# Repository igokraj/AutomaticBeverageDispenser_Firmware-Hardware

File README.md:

# Automatic Beverage Dispenser

A complete hardware and software solution for an automated beverage dispensing system. The project features a custom 2-layer printed circuit board (PCB) and firmware written in C for the STM32G0 microcontroller. The system accurately dispenses liquids by measuring the flow rate via a dedicated sensor and controlling a 12V fluid pump.

## Features
* **Adjustable Volume Control:** Users can set the desired liquid volume between 50 ml and 300 ml (in 50 ml increments) using the "Up" and "Down" tactile switches.
* **Precise Dispensing:** Utilizes an external flow sensor with interrupt-driven pulse counting to accurately measure the dispensed volume based on a configurable K-factor.
* **Automated Pump Control:** The MCU controls a 12V DC fluid pump via an onboard N-channel MOSFET (AO3400), automatically shutting it off once the target volume is reached.
* **Emergency Stop:** The pouring process can be manually halted at any time by pressing the "Start/Stop" button.
* **Expansion Ready:** Exposed I2C headers allow for future integration of external modules, such as an OLED display.

## Hardware Specifications
* **Microcontroller:** STM32G030F6P6 (ARM Cortex-M0+)
* **Power Supply:** 12V DC input (barrel jack), regulated to 3.3V for logic via an AMS1117 LDO.
* **Actuator Driver:** AO3400 MOSFET with flyback diode protection for the 12V pump.
* **Inputs:** 3x Tactile switches (hardware debounced/filtered), 1x Flow sensor signal input.
* **Interfaces:** SWD programming header, I2C expansion header.

## Software
The firmware is developed using STM32 HAL. It implements a simple state machine (`IDLE` and `POURING`) to manage user inputs and the dispensing process. Button inputs are software-debounced, and the flow sensor is handled via external interrupts (EXTI) to ensure no pulses are missed during the pump operation.

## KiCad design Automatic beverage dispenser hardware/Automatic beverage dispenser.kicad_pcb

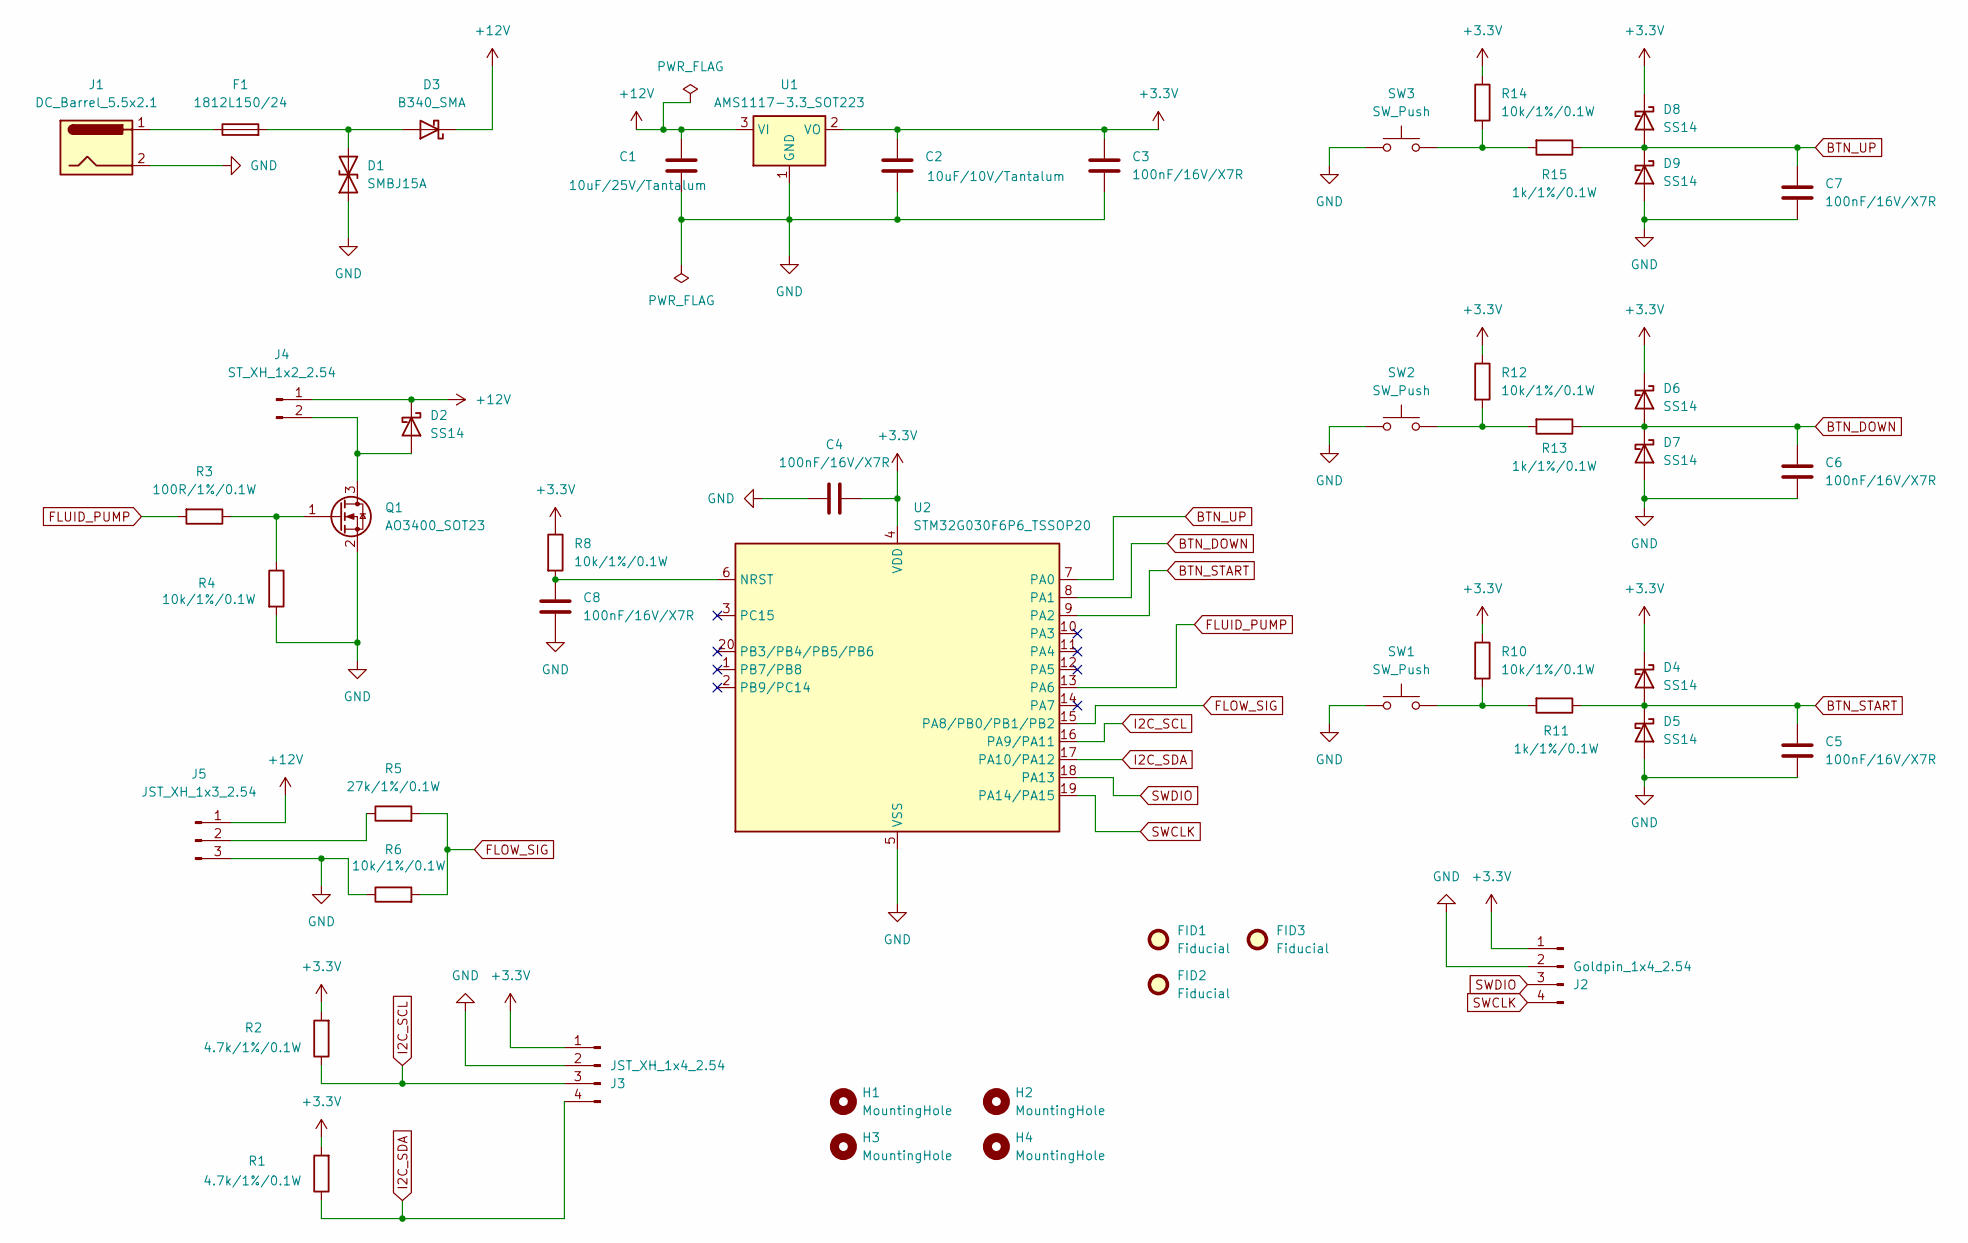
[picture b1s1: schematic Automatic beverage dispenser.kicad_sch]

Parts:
C1: 10uF/25V/Tantalum; CP_EIA-3216-18_Kemet-A; LCSC Part # C13585
C2: 10uF/10V/Tantalum; CP_EIA-3216-18_Kemet-A; LCSC Part # C7177
C3, C4, C5, C6, C7, C8: 100nF/16V/X7R; C_0805_2012Metric; LCSC Part # C49678
D1: SMBJ15A; D_SMB; LCSC Part # C10210
D2, D4, D5, D6, D7, D8, D9: SS14; D_SMA; LCSC Part # C2168
D3: B340_SMA; D_SMA; LCSC Part # C64982
F1: 1812L150/24; Fuse_1812_4532Metric; LCSC Part # C9308
FID1, FID2, FID3: Fiducial; Fiducial_1mm_Mask2mm
H1, H2, H3, H4: MountingHole; MountingHole_2.2mm_M2
J1: DC_Barrel_5.5x2.1; BarrelJack_Horizontal
J2: Goldpin_1x4_2.54; PinHeader_1x04_P2.54mm_Vertical
J3: JST_XH_1x4_2.54; JST_XH_B4B-XH-A_1x04_P2.50mm_Vertical
J4: ST_XH_1x2_2.54; JST_XH_B2B-XH-A_1x02_P2.50mm_Vertical
J5: JST_XH_1x3_2.54; JST_XH_B3B-XH-A_1x03_P2.50mm_Vertical
Q1: AO3400_SOT23; SOT-23; LCSC Part # C20917
R1, R2: 4.7k/1%/0.1W; R_0805_2012Metric; LCSC Part # C17673
R3: 100R/1%/0.1W; R_0805_2012Metric; LCSC Part # C17408
R4, R6, R8, R10, R12, R14: 10k/1%/0.1W; R_0805_2012Metric; LCSC Part # C17414
R5: 27k/1%/0.1W; R_0805_2012Metric; LCSC Part # C2904543
R11, R13, R15: 1k/1%/0.1W; R_0805_2012Metric; LCSC Part # C17513
SW1, SW2, SW3: SW_Push; SW_PUSH_6mm_H5mm
U1: AMS1117-3.3_SOT223; SOT-223-3_TabPin2; LCSC Part # C6186
U2: STM32G030F6P6_TSSOP20; TSSOP-20_4.4x6.5mm_P0.65mm; LCSC Part # C529330

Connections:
+3.3V: C2.1, C3.1, C4.2, D4.1 (K), D6.1 (K), D8.1 (K), J2.1, J3.1, R1.2, R2.2, R8.1, R10.1, R12.1, R14.1, U1.2 (VO), U2.4 (VDD)
+12V: C1.1, D2.1 (K), D3.1 (K), J4.1, J5.1, U1.3 (VI)
BTN_DOWN: C6.2, D6.2 (A), D7.1 (K), R13.1, U2.8 (PA1)
BTN_START: C5.2, D4.2 (A), D5.1 (K), R11.1, U2.9 (PA2)
BTN_UP: C7.2, D8.2 (A), D9.1 (K), R15.1, U2.7 (PA0)
FLOW_SIG: R5.2, R6.2, U2.15 (PA8/PB0/PB1/PB2)
FLUID_PUMP: R3.2, U2.13 (PA6)
GND: C1.2, C2.2, C3.2, C4.1, C5.1, C6.1, C7.1, C8.1, D1.1 (A1), D5.2 (A), D7.2 (A), D9.2 (A), J1.2, J2.2, J3.2, J5.3, Q1.2 (S), R4.2, R6.1, SW1.1, SW2.1, SW3.1, U1.1 (GND), U2.5 (VSS)
I2C_SCL: J3.3, R2.1, U2.16 (PA9/PA11)
I2C_SDA: J3.4, R1.1, U2.17 (PA10/PA12)
unnamed: D1.2 (A2), D3.2 (A), F1.2
unnamed: D2.2 (A), J4.2, Q1.3 (D)
unnamed: F1.1, J1.1
unnamed: J5.2, R5.1
unnamed: Q1.1 (G), R3.1, R4.1
unnamed: R10.2, R11.2, SW1.2
unnamed: R12.2, R13.2, SW2.2
unnamed: R14.2, R15.2, SW3.2
unnamed: C8.2, R8.2, U2.6 (NRST)
SWCLK: J2.4, U2.19 (PA14/PA15)
SWDIO: J2.3, U2.18 (PA13)

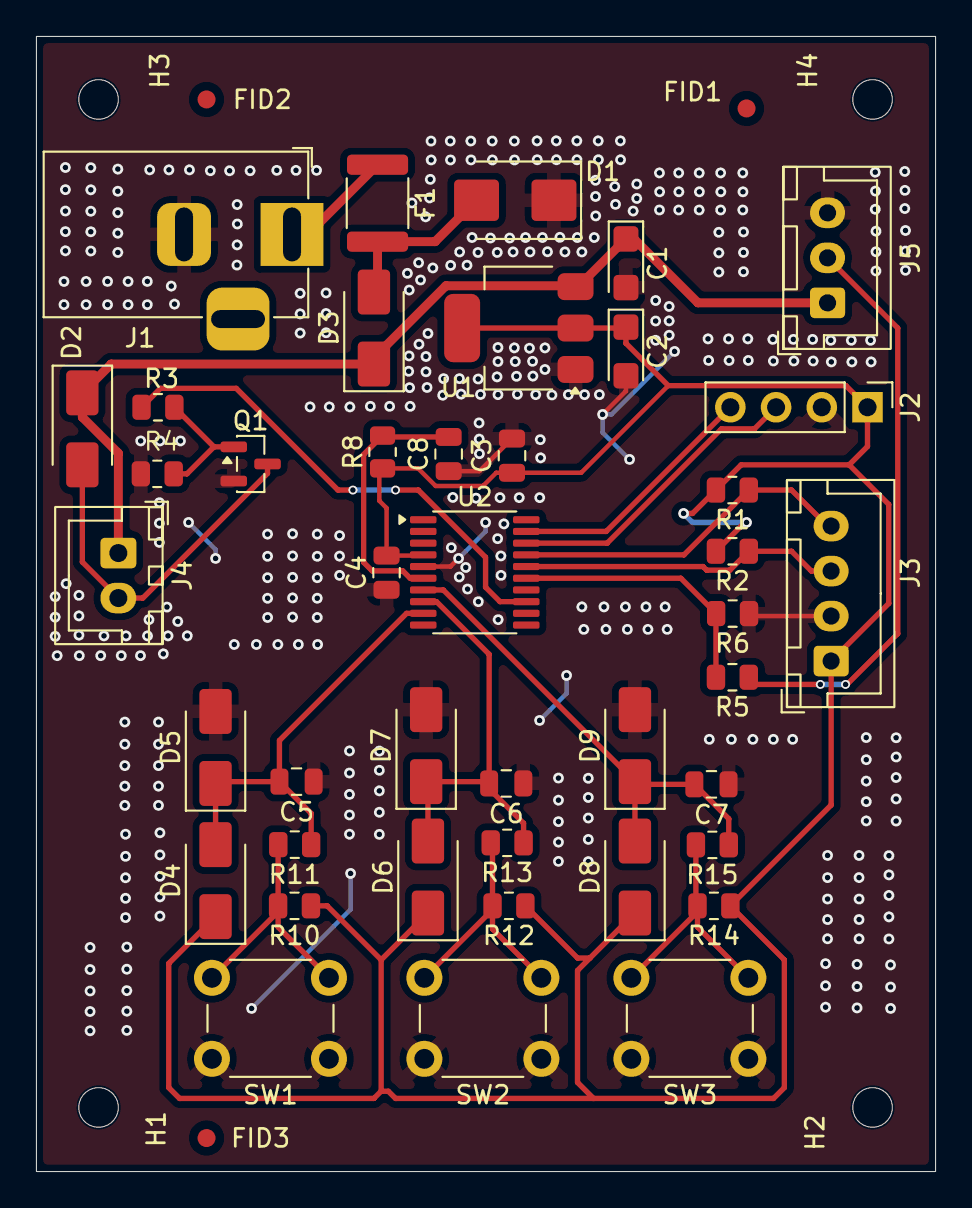
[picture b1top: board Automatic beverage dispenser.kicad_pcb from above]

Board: 2 copper layers, 49.9 x 63.1 mm, 49 parts (0 on the bottom side), 21 nets.

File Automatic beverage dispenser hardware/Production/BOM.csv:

Reference;Qty;Value;DNP;Exclude from BOM;Exclude from Board;Footprint;Datasheet;LCSC Part #
C1;1;10uF/25V/Tantalum;;;;Capacitor_Tantalum_SMD:CP_EIA-3216-18_Kemet-A;;C13585
C2;1;10uF/10V/Tantalum;;;;Capacitor_Tantalum_SMD:CP_EIA-3216-18_Kemet-A;;C7177
C3,C4,C5,C6,C7,C8;6;100nF/16V/X7R;;;;Capacitor_SMD:C_0805_2012Metric;;C49678
D1;1;SMBJ15A;;;;Diode_SMD:D_SMB;;C10210
D2,D4,D5,D6,D7,D8,D9;7;SS14;;;;Diode_SMD:D_SMA;;C2168
D3;1;B340_SMA;;;;Diode_SMD:D_SMA;;C64982
F1;1;1812L150/24;;;;Fuse:Fuse_1812_4532Metric;;C9308
J1;1;DC_Barrel_5.5x2.1;;;;Connector_BarrelJack:BarrelJack_Horizontal;;
J2;1;Goldpin_1x4_2.54;;;;Connector_PinHeader_2.54mm:PinHeader_1x04_P2.54mm_Vertical;;
J3;1;JST_XH_1x4_2.54;;;;Connector_JST:JST_XH_B4B-XH-A_1x04_P2.50mm_Vertical;;
J4;1;ST_XH_1x2_2.54;;;;Connector_JST:JST_XH_B2B-XH-A_1x02_P2.50mm_Vertical;;
J5;1;JST_XH_1x3_2.54;;;;Connector_JST:JST_XH_B3B-XH-A_1x03_P2.50mm_Vertical;;
Q1;1;AO3400_SOT23;;;;Package_TO_SOT_SMD:SOT-23;;C20917
R1,R2;2;4.7k/1%/0.1W;;;;Resistor_SMD:R_0805_2012Metric;;C17673
R3;1;100R/1%/0.1W;;;;Resistor_SMD:R_0805_2012Metric;;C17408
R4,R6,R8,R10,R12,R14;6;10k/1%/0.1W;;;;Resistor_SMD:R_0805_2012Metric;;C17414
R5;1;27k/1%/0.1W;;;;Resistor_SMD:R_0805_2012Metric;;C2904543
R11,R13,R15;3;1k/1%/0.1W;;;;Resistor_SMD:R_0805_2012Metric;;C17513
SW1,SW2,SW3;3;SW_Push;;;;Button_Switch_THT:SW_PUSH_6mm_H5mm;;
U1;1;AMS1117-3.3_SOT223;;;;Package_TO_SOT_SMD:SOT-223-3_TabPin2;http://www.advanced-monolithic.com/pdf/ds1117.pdf;C6186
U2;1;STM32G030F6P6_TSSOP20;;;;Package_SO:TSSOP-20_4.4x6.5mm_P0.65mm;https://www.st.com/resource/en/datasheet/stm32g030f6.pdf;C529330
;;;;;;;;
;;;;;;;;
;;;;;;;;
;;;;;;;;
;;;;;;;;
;;;;;;;;

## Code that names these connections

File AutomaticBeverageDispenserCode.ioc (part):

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Mcu.Name=STM32G030F6Px
Mcu.Package=TSSOP20
Mcu.UserName=STM32G030F6Px
PA0.GPIOParameters=GPIO_Label
PA0.GPIO_Label=UP_BUTTON
PA0.Signal=GPIO_Input
PA1.GPIOParameters=GPIO_Label
PA1.GPIO_Label=DOWN_BUTTON
PA1.Signal=GPIO_Input
PA11\ [PA9].Mode=I2C
PA11\ [PA9].Signal=I2C2_SCL
PA12\ [PA10].Mode=I2C
PA12\ [PA10].Signal=I2C2_SDA
PA13.Mode=Serial_Wire
PA13.Signal=SYS_SWDIO
PA14-BOOT0.Mode=Serial_Wire
PA14-BOOT0.Signal=SYS_SWCLK
PA14-BOOT0__PA15.StandardMode=true
PA2.Signal=GPXTI2
PA6.GPIOParameters=GPIO_Label
PA6.GPIO_Label=PUMP
PA6.Signal=GPIO_Output
PB0.Signal=GPXTI0
PB0__PB1__PB2__PA8.StandardMode=true
PB3__PB4__PB5__PB6.StandardMode=true
PB7__PB8.StandardMode=true
PC14-OSC32_IN\ (PC14)__PB9.StandardMode=true
RCC.HSE_VALUE=8000000
RCC.SYSCLKFreq_VALUE=16000000
board=custom

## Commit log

2026-06-17 Update README with images and project description
    Added images for schematic, PCB design, and 3D view.
2026-06-17 Update README.md by removing images
    Removed two images from the README file.
2026-06-17 Added Hardware and images
2026-06-17 Fixed CubeMX
2026-06-17 Comment corrected
2026-06-20 Added Display functions
